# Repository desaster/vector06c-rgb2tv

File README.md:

This is [Improver's RGB2TV](https://zx-pk.ru/threads/8739-vektor-06ts-videovykhod-podklyuchenie-k-tv.html?p=981527&viewfull=1#post981527) recreated in KiCAD

**NOTE: I have not been able to get composite or s-video output (CXA2075M) working on this board. It works fine for fixing sync & colors, though.**

Changes to the original design:

* Outputs for R, G, B and S-Video
* Some components are smaller
* Board layout is not as pretty

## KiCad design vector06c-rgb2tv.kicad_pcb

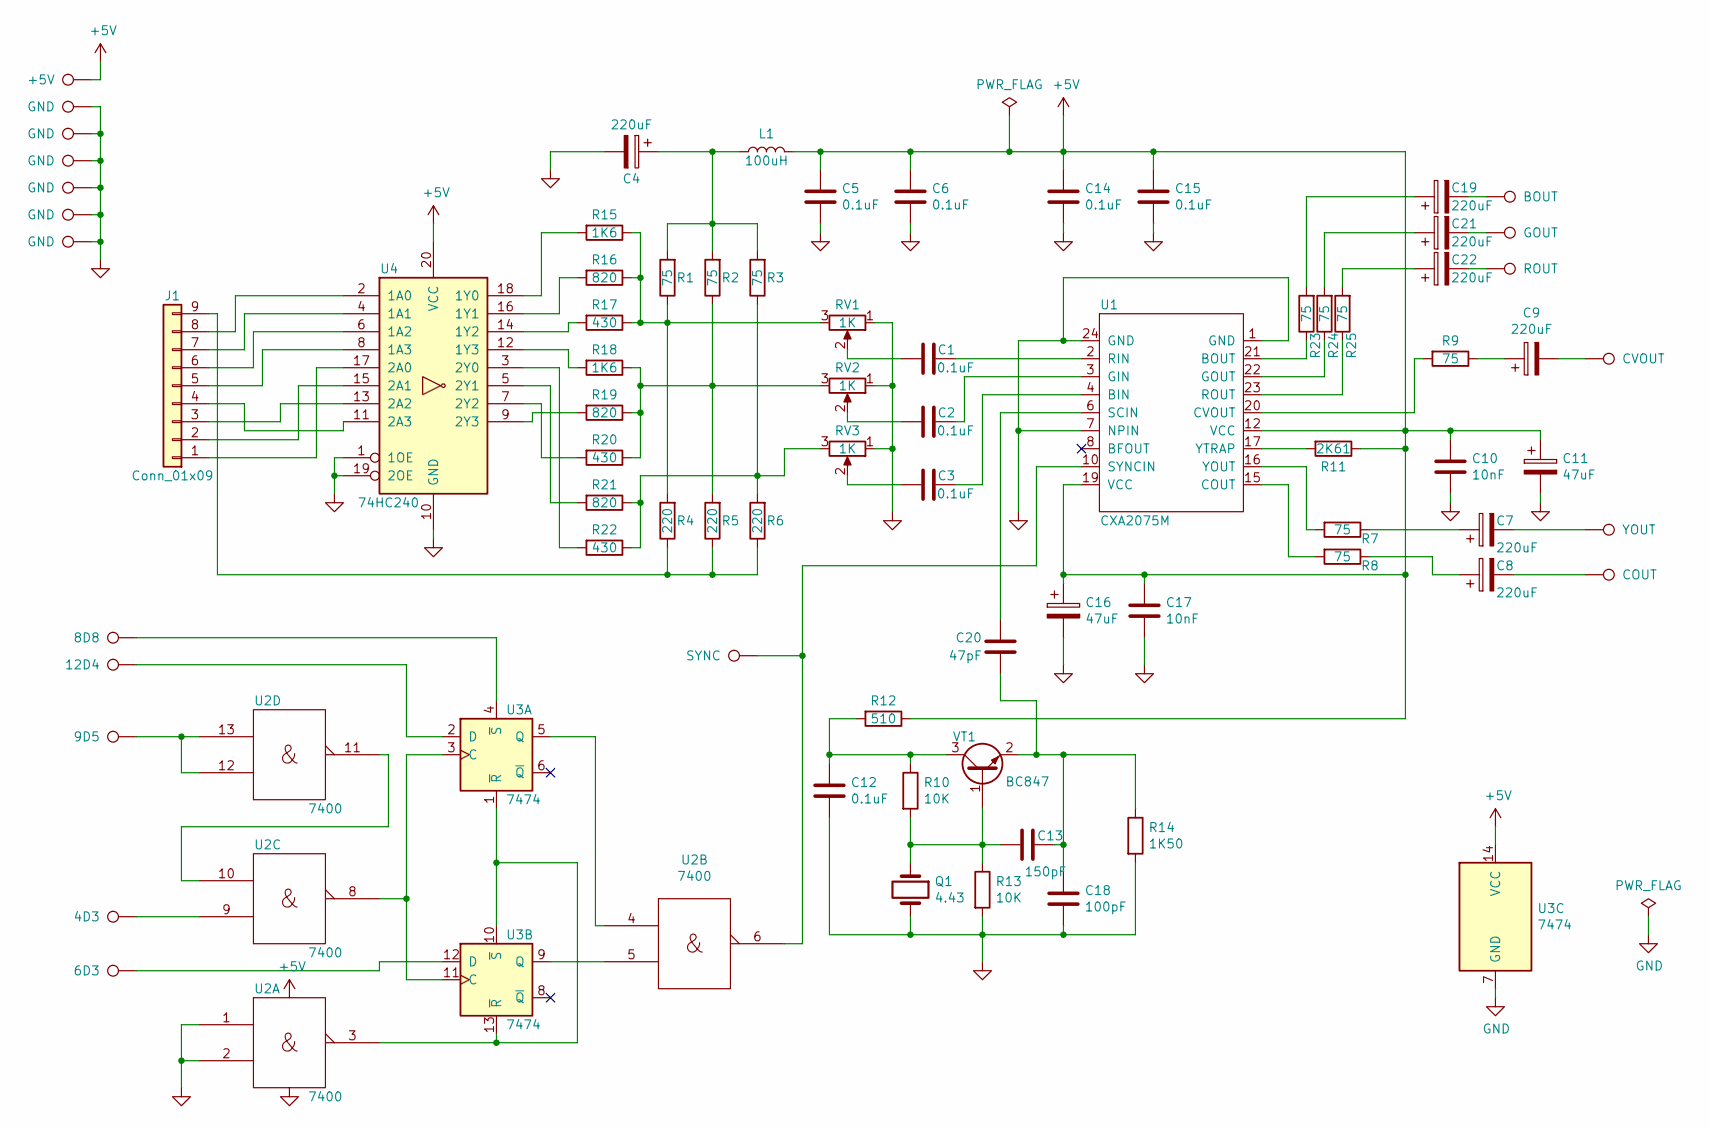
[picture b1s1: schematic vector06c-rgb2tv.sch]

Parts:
C1, C2, C3, C5, C6, C12, C14, C15: 0.1uF; C_0805_2012Metric_Pad1.15x1.40mm_HandSolder
C4, C7, C8, C9, C19, C21, C22: 220uF; CP_EIA-3528-15_AVX-H_Pad1.50x2.35mm_HandSolder
C10, C17: 10nF; C_0805_2012Metric_Pad1.15x1.40mm_HandSolder
C11, C16: 47uF; CP_EIA-3528-15_AVX-H_Pad1.50x2.35mm_HandSolder
C13: 150pF; C_0805_2012Metric_Pad1.15x1.40mm_HandSolder
C18: 100pF; C_0805_2012Metric_Pad1.15x1.40mm_HandSolder
C20: 47pF; C_0805_2012Metric_Pad1.15x1.40mm_HandSolder
J1: Conn_01x09; PinHeader_1x09_P2.54mm_Vertical
L1: 100uH; L_1210_3225Metric_Pad1.42x2.65mm_HandSolder
Q1: 4.43; Crystal_HC49-4H_Vertical
R1, R2, R3, R7, R8, R9, R23, R24, R25: 75; R_0805_2012Metric_Pad1.15x1.40mm_HandSolder
R4, R5, R6: 220; R_0805_2012Metric_Pad1.15x1.40mm_HandSolder
R10, R13: 10K; R_0805_2012Metric_Pad1.15x1.40mm_HandSolder
R11: 2K61; R_0805_2012Metric_Pad1.15x1.40mm_HandSolder
R12: 510; R_0805_2012Metric_Pad1.15x1.40mm_HandSolder
R14: 1K50; R_0805_2012Metric_Pad1.15x1.40mm_HandSolder
R15, R18: 1K6; R_0805_2012Metric_Pad1.15x1.40mm_HandSolder
R16, R19, R21: 820; R_0805_2012Metric_Pad1.15x1.40mm_HandSolder
R17, R20, R22: 430; R_0805_2012Metric_Pad1.15x1.40mm_HandSolder
RV1, RV2, RV3: 1K; Potentiometer_Bourns_3296W_Vertical
TP1: 8D8; PAD-150-60
TP2: 12D4; PAD-150-60
TP3: 9D5; PAD-150-60
TP4: 4D3; PAD-150-60
TP5: 6D3; PAD-150-60
TP6: SYNC; PAD-150-60
TP7: CVOUT; PAD-150-60
TP8: +5V; PAD-150-60
TP9, TP10, TP16, TP17, TP18, TP19: GND; PAD-150-60
TP11: BOUT; PAD-150-60
TP12: GOUT; PAD-150-60
TP13: ROUT; PAD-150-60
TP14: YOUT; PAD-150-60
TP15: COUT; PAD-150-60
U1: CXA2075M; SOIC-24W_7.5x15.4mm_P1.27mm
U2: 7400; SOIC-14_3.9x8.7mm_P1.27mm
U3: 7474; SOIC-14_3.9x8.7mm_P1.27mm
U4: 74HC240; SOIC-20W_7.5x12.8mm_P1.27mm
VT1: BC847; SOT-23

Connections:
+5V: C5.1, C6.1, C10.1, C11.1, C14.1, C15.1, C16.1, C17.1, L1.2, R11.1, R12.1, TP8.1, U1.12 (VCC), U1.19 (VCC), U2.14 (Vcc), U3.14 (VCC), U4.20 (VCC)
GND: C4.2, C5.2, C6.2, C10.2, C11.2, C12.2, C14.2, C15.2, C16.2, C17.2, C18.2, Q1.2, R13.2, R14.2, RV1.1, RV2.1, RV3.1, TP9.1, TP10.1, TP16.1, TP17.1, TP18.1, TP19.1, U1.1 (GND), U1.7 (NPIN), U1.24 (GND), U2.1, U2.2, U2.7 (GND), U3.7 (GND), U4.1 (1OE), U4.10 (GND), U4.19 (2OE)
unnamed: C1.1, U1.2 (RIN)
unnamed: C1.2, RV1.2
unnamed: C2.1, U1.3 (GIN)
unnamed: C2.2, RV2.2
unnamed: C3.1, U1.4 (BIN)
unnamed: C3.2, RV3.2
unnamed: C4.1, L1.1, R1.2, R2.2, R3.2
unnamed: C7.1, R7.1
unnamed: C7.2, TP14.1
unnamed: C8.1, R8.1
unnamed: C8.2, TP15.1
unnamed: C9.1, R9.1
unnamed: C9.2, TP7.1
unnamed: C12.1, R10.1, R12.2, VT1.3 (C)
unnamed: C13.1, C18.1, C20.2, R14.1, VT1.2 (E)
unnamed: C13.2, Q1.1, R10.2, R13.1, VT1.1 (B)
unnamed: C19.1, R23.2
unnamed: C19.2, TP11.1
unnamed: C20.1, U1.6 (SCIN)
unnamed: C21.1, R24.2
unnamed: C21.2, TP12.1
unnamed: C22.1, R25.2
unnamed: C22.2, TP13.1
unnamed: J1.1, U4.17 (2A0)
unnamed: J1.2, U4.15 (2A1)
unnamed: J1.3, U4.13 (2A2)
unnamed: J1.4, U4.11 (2A3)
unnamed: J1.5, U4.8 (1A3)
unnamed: J1.6, U4.6 (1A2)
unnamed: J1.7, U4.4 (1A1)
unnamed: J1.8, U4.2 (1A0)
unnamed: J1.9, R4.1, R5.1, R6.1
unnamed: R1.1, R4.2, R15.1, R16.1, R17.1, RV1.3
unnamed: R7.2, U1.16 (YOUT)
unnamed: R8.2, U1.15 (COUT)
unnamed: R9.2, U1.20 (CVOUT)
unnamed: R11.2, U1.17 (YTRAP)
unnamed: R15.2, U4.18 (1Y0)
unnamed: R16.2, U4.16 (1Y1)
unnamed: R17.2, U4.14 (1Y2)
unnamed: R2.1, R5.2, R18.1, R19.1, R20.1, RV2.3
unnamed: R18.2, U4.12 (1Y3)
unnamed: R19.2, U4.9 (2Y3)
unnamed: R20.2, U4.7 (2Y2)
unnamed: R3.1, R6.2, R21.1, R22.1, RV3.3
unnamed: R21.2, U4.5 (2Y1)
unnamed: R22.2, U4.3 (2Y0)
unnamed: R23.1, U1.21 (BOUT)
unnamed: R24.1, U1.22 (GOUT)
unnamed: R25.1, U1.23 (ROUT)
unnamed: TP1.1, U3.4 (~S)
unnamed: TP2.1, U3.2 (D)
unnamed: TP3.1, U2.12, U2.13
unnamed: TP4.1, U2.9
unnamed: TP5.1, U3.12 (D)
unnamed: TP6.1, U1.10 (SYNCIN), U2.6
unnamed: U2.3, U3.1 (~R), U3.10 (~S), U3.13 (~R)
unnamed: U2.4, U3.5 (Q)
unnamed: U2.5, U3.9 (Q)
unnamed: U2.8, U3.3 (C), U3.11 (C)
unnamed: U2.10, U2.11

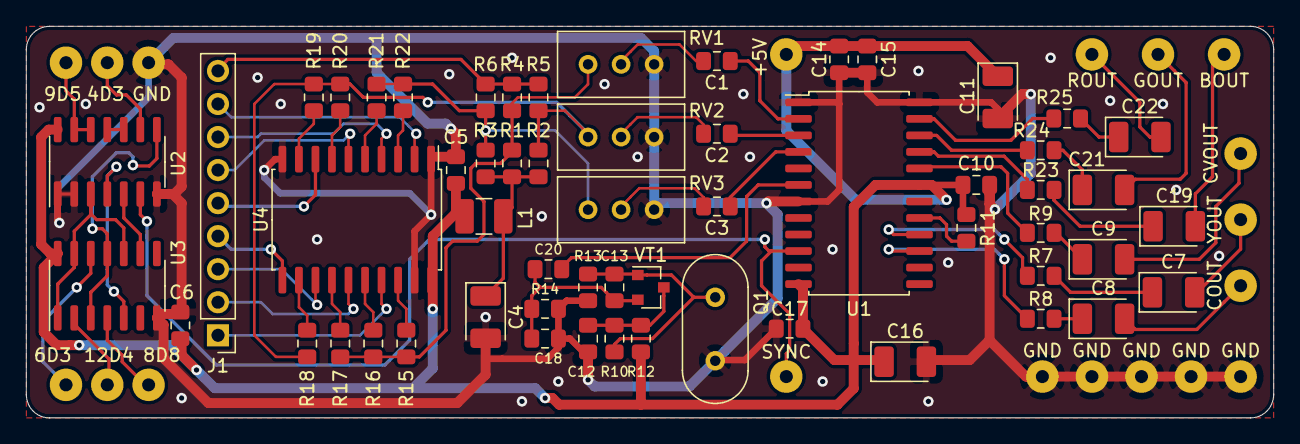
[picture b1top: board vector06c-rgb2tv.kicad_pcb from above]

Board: 2 copper layers, 95.9 x 30.1 mm, 77 parts (0 on the bottom side), 63 nets.

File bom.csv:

"Id";"Designator";"Package";"Quantity";"Designation";"Supplier and ref";
1;"TP3";"PAD-150-60";1;"9D5";;;
2;"J1";"PinHeader_1x09_P2.54mm_Vertical";1;"Conn_01x09";;;
3;"L1";"L_1210_3225Metric_Pad1.42x2.65mm_HandSolder";1;"100uH";;;
4;"Q1";"Crystal_HC49-4H_Vertical";1;"4.43";;;
5;"TP1";"PAD-150-60";1;"8D8";;;
6;"TP2";"PAD-150-60";1;"12D4";;;
7;"TP4";"PAD-150-60";1;"4D3";;;
8;"TP5";"PAD-150-60";1;"6D3";;;
9;"TP6";"PAD-150-60";1;"SYNC";;;
10;"TP7";"PAD-150-60";1;"CVOUT";;;
11;"U1";"SOIC-24W_7.5x15.4mm_P1.27mm";1;"CXA2075M";;;
12;"U2";"SOIC-14_3.9x8.7mm_P1.27mm";1;"7400";;;
13;"U3";"SOIC-14_3.9x8.7mm_P1.27mm";1;"7474";;;
14;"U4";"SOIC-20W_7.5x12.8mm_P1.27mm";1;"74HC240";;;
15;"VT1";"SOT-23";1;"BC847";;;
16;"RV1,RV2,RV3";"Potentiometer_Bourns_3296W_Vertical";3;"1K";;;
17;"TP8";"PAD-150-60";1;"+5V";;;
18;"TP9,TP10,TP16,TP17,TP18,TP19";"PAD-150-60";6;"GND";;;
19;"C1,C2,C3,C5,C6,C12,C14,C15";"C_0805_2012Metric_Pad1.15x1.40mm_HandSolder";8;"0.1uF";;;
20;"C10,C17";"C_0805_2012Metric_Pad1.15x1.40mm_HandSolder";2;"10nF";;;
21;"C13";"C_0805_2012Metric_Pad1.15x1.40mm_HandSolder";1;"150pF";;;
22;"C18";"C_0805_2012Metric_Pad1.15x1.40mm_HandSolder";1;"100pF";;;
23;"C20";"C_0805_2012Metric_Pad1.15x1.40mm_HandSolder";1;"47pF";;;
24;"R1,R2,R3,R9,R7,R8,R23,R24,R25";"R_0805_2012Metric_Pad1.15x1.40mm_HandSolder";9;"75";;;
25;"R4,R5,R6";"R_0805_2012Metric_Pad1.15x1.40mm_HandSolder";3;"220";;;
26;"R10,R13";"R_0805_2012Metric_Pad1.15x1.40mm_HandSolder";2;"10K";;;
27;"R11";"R_0805_2012Metric_Pad1.15x1.40mm_HandSolder";1;"2K61";;;
28;"R12";"R_0805_2012Metric_Pad1.15x1.40mm_HandSolder";1;"510";;;
29;"R14";"R_0805_2012Metric_Pad1.15x1.40mm_HandSolder";1;"1K50";;;
30;"R15,R18";"R_0805_2012Metric_Pad1.15x1.40mm_HandSolder";2;"1K6";;;
31;"R16,R19,R21";"R_0805_2012Metric_Pad1.15x1.40mm_HandSolder";3;"820";;;
32;"R17,R20,R22";"R_0805_2012Metric_Pad1.15x1.40mm_HandSolder";3;"430";;;
33;"TP11";"PAD-150-60";1;"BOUT";;;
34;"TP12";"PAD-150-60";1;"GOUT";;;
35;"TP13";"PAD-150-60";1;"ROUT";;;
36;"TP14";"PAD-150-60";1;"YOUT";;;
37;"TP15";"PAD-150-60";1;"COUT";;;
38;"C4,C7,C8,C9,C19,C21,C22";"CP_EIA-3528-15_AVX-H_Pad1.50x2.35mm_HandSolder";7;"220uF";;;
39;"C11,C16";"CP_EIA-3528-15_AVX-H_Pad1.50x2.35mm_HandSolder";2;"47uF";;;

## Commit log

2020-06-02 add referenfe image
2020-06-02 add board picture
2020-06-02 change readme
2020-06-02 rename project files, fix Improver's nick
2020-06-12 fix silkscreen layout
2020-06-24 fix C4 orientation
2020-09-22 added note about output problems
